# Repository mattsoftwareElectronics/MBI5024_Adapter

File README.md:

# MBI5024_Adapter
Adapter for the MBI5024 LED Driver Chip to convert for a breadboard

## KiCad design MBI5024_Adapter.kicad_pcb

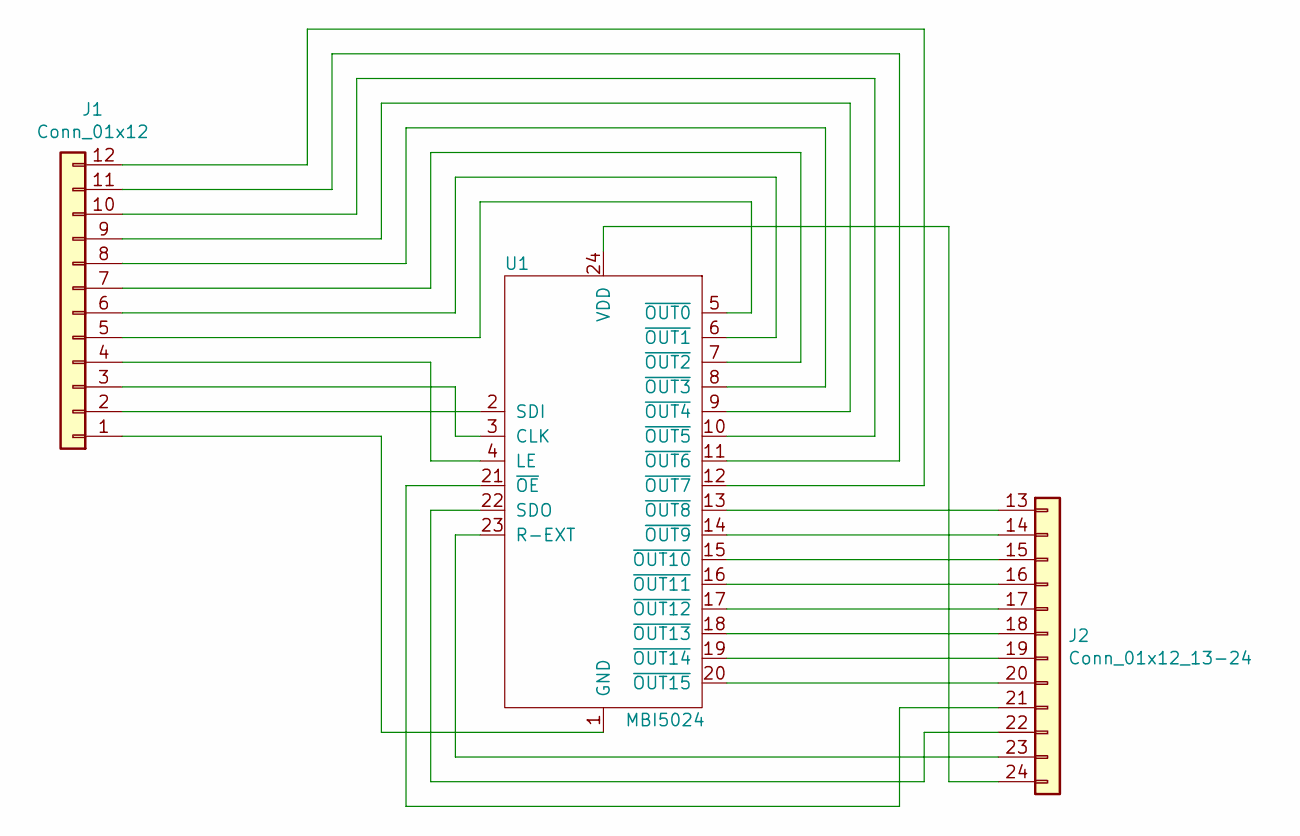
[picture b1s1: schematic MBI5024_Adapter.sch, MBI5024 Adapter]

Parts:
J1: Conn_01x12; PinHeader_1x12_P2.54mm_Vertical
J2: Conn_01x12_13-24; PinHeader_1x12_P2.54mm_Vertical_13-24
U1: MBI5024; SSOP-24-1mm

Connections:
unnamed: J1.1, U1.1 (GND)
unnamed: J1.2, U1.2 (SDI)
unnamed: J1.3, U1.3 (CLK)
unnamed: J1.4, U1.4 (LE)
unnamed: J1.5, U1.5 (~OUT0)
unnamed: J1.6, U1.6 (~OUT1)
unnamed: J1.7, U1.7 (~OUT2)
unnamed: J1.8, U1.8 (~OUT3)
unnamed: J1.9, U1.9 (~OUT4)
unnamed: J1.10, U1.10 (~OUT5)
unnamed: J1.11, U1.11 (~OUT6)
unnamed: J1.12, U1.12 (~OUT7)
unnamed: J2.13 (Pin_1), U1.13 (~OUT8)
unnamed: J2.14 (Pin_2), U1.14 (~OUT9)
unnamed: J2.15 (Pin_3), U1.15 (~OUT10)
unnamed: J2.16 (Pin_4), U1.16 (~OUT11)
unnamed: J2.17 (Pin_5), U1.17 (~OUT12)
unnamed: J2.18 (Pin_6), U1.18 (~OUT13)
unnamed: J2.19 (Pin_7), U1.19 (~OUT14)
unnamed: J2.20 (Pin_8), U1.20 (~OUT15)
unnamed: J2.21 (Pin_9), U1.21 (~OE)
unnamed: J2.22 (Pin_10), U1.22 (SDO)
unnamed: J2.23 (Pin_11), U1.23 (R-EXT)
unnamed: J2.24 (Pin_12), U1.24 (VDD)

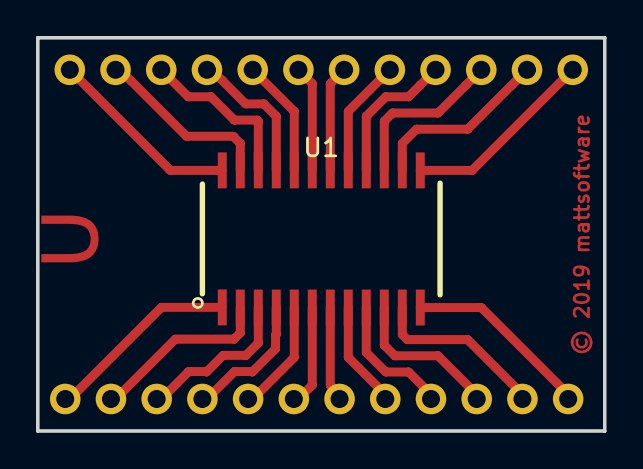
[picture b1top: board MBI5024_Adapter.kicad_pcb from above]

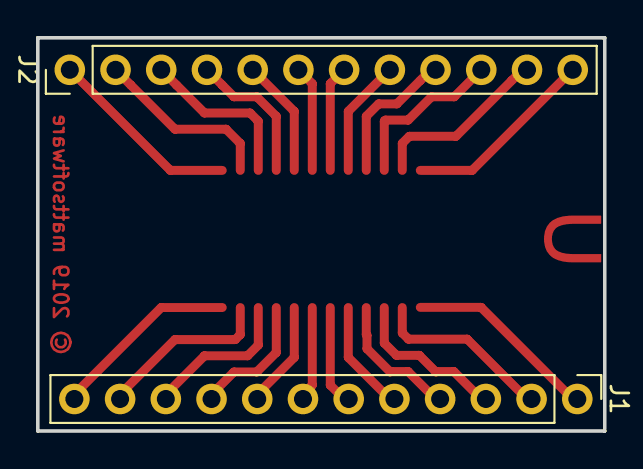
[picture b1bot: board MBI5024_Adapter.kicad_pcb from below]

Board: 2 copper layers, 31.5 x 21.8 mm, 3 parts (2 on the bottom side), 24 nets.

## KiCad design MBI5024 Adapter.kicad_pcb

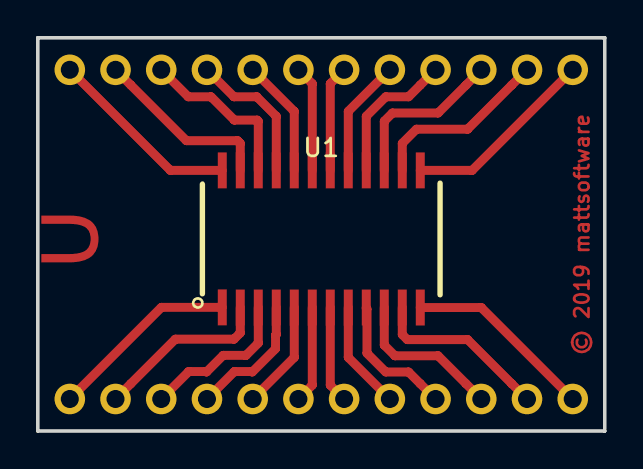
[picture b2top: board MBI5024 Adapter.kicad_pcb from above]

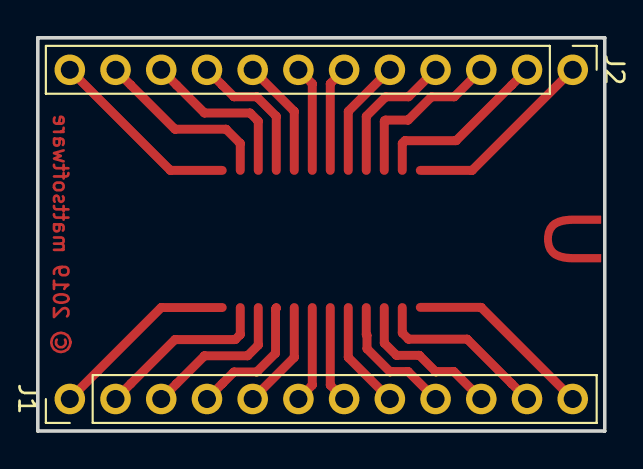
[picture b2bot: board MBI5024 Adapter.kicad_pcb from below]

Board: 2 copper layers, 31.5 x 21.8 mm, 3 parts (2 on the bottom side), 24 nets.

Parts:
J1, J2: Conn_01x12; PinHeader_1x12_P2.54mm_Vertical
U1: MBI5024; SSOP-24-1mm

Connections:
unnamed: J1.1, U1.12
unnamed: J1.2, U1.11
unnamed: J1.3, U1.10
unnamed: J1.4, U1.9
unnamed: J1.5, U1.8
unnamed: J1.6, U1.7
unnamed: J1.7, U1.6
unnamed: J1.8, U1.5
unnamed: J1.9, U1.4
unnamed: J1.10, U1.3
unnamed: J1.11, U1.2
unnamed: J1.12, U1.1
unnamed: J2.1, U1.24
unnamed: J2.2, U1.23
unnamed: J2.3, U1.22
unnamed: J2.4, U1.21
unnamed: J2.5, U1.20
unnamed: J2.6, U1.19
unnamed: J2.7, U1.18
unnamed: J2.8, U1.17
unnamed: J2.9, U1.16
unnamed: J2.10, U1.15
unnamed: J2.11, U1.14
unnamed: J2.12, U1.13

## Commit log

2019-01-20 Initial project before re-aranging
2019-01-20 Rename the footprint library
2019-01-20 Renamed 3d file
2019-01-20 Removed the bak file
2019-01-20 Change project name to MBI5024
2019-01-20 Fix up schematic for the adapter
2019-01-20 Fixed up PCB
2019-01-20 Added link to datasheet
2019-01-20 Added the remote MBI5024 project to hold the specific kicad files
2019-01-20 Updated MBI5024 project
2019-01-20 Moved footprint to the submodule
2019-01-20 Updated submodule
2019-01-20 Move the symbol library to the submodule
2019-01-20 Renamed project
2019-01-20 Generate new pcb to make sure the pipeline works

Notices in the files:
MBI5024 Adapter.kicad_pcb:
License: CC BY 4.0
© 2019 mattsoftware
MBI5024_Adapter.sch:
creativecommons.org/licences/by/4.0
Licence: CC By 4.0
